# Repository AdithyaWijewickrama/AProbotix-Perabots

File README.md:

# AProbotix-Perabots

This repo holds team AProbotix's work for the PeraBots 2026 competition
(University category), Faculty of Engineering, University of Ruhuna.

| Folder | Round | What it is |
|---|---|---|
| [`Phase 01 - Online Round/`](Phase%2001%20-%20Online%20Round/) | Online (simulation) round | Webots solution submitted for round 1. Includes the TwoWheelRobot controller, test worlds, the sim lab and the submission zip builder |
| [`Phase 02 - Final Round/`](Phase%2002%20-%20Final%20Round/) | Final (physical) round – "The Nine Seals of Pera" | GuardianBot: Webots simulation of all 3 trials, plus the hardware (PCB, laser-cut acrylic, 3-D prints, parts list and build guide) |

## Phase 01 – Online Round

This is the original first-round project, moved into its own folder unchanged. Paths below
are relative to `Phase 01 - Online Round/`:

- `controllers/`, `protos/`, `worlds/`: working copy with comments. Open `worlds/Arena.wbt` in Webots R2025a.
- `submission/`: clean copy built by `make_submission_zip.py` (do not edit by hand).
- `test/`: test worlds, test report, tools and the sim lab (`test/tools/lab/start_lab.bat`).
- `CONTROLLER_EXPLANATION.md`, `DEVELOPMENT_NOTES.md`: write-ups of the controller.

## Phase 02 – Final Round

Start with [`Phase 02 - Final Round/README.md`](Phase%2002%20-%20Final%20Round/README.md).
Quick links:

- Simulation: open `Phase 02 - Final Round/simulation/worlds/perabots_arena.wbt` in Webots R2025a.
- Build guide and parts list: `Phase 02 - Final Round/docs/GuardianBot_build_guide_and_BOM.md`.
- PCB to order: `Phase 02 - Final Round/hardware/pcb/guardianbot_main_gerbers_JLCPCB.zip`.
- Laser cutting: `Phase 02 - Final Round/hardware/acrylic/`. 3-D printing: `Phase 02 - Final Round/hardware/3d_prints/`.

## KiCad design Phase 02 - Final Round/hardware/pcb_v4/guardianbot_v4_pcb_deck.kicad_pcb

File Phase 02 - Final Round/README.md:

# Phase 02 – Final Round: "The Nine Seals of Pera"

PeraBots 2026, University category, final round (physical robot) – team AProbotix.

Our robot is **GuardianBot v4.2**: a 150 mm round robot built from the parts the team really owns. v4.2 is v4.1 with the camera on an SG90 tilt servo, so one look reads the whole Section 3 board (`test/FIXES.md`, Fix 4); the tilting camera mast is in `hardware/3d_prints` (camera_mast + camera_tilt_bracket).

- **Controllers:**
  - Arduino Mega 2560: real-time body, mounted upside-down on the PCB deck.
  - ESP32-S3 N16R8 with an OV7670 camera: brain on core 1, camera on core 0. It sees maze tiles 1–2 cells ahead.
- **Drive:** DRV8833 with two 6 V 300 rpm N20 encoder motors, on a 2S LiPo.
- **Sensors:**
  - 8 × VL53L0X time-of-flight: front, ±45°, two per side for wall alignment, back
  - 2 × HC-SR04
  - 2 × TCS3200 colour: floor tiles and piece colour
  - Pololu QTR-8RC line array
  - L3G4200D gyro
- **User interface:** 1 × 4 keypad and a 128 × 32 OLED.
- **Gripper:** a rear capture pocket with two Kpower M0170 servo arms.
- **Middle floor:** a PCB that carries all the wiring, with keyed JST-XH sockets. A vero board can replace it.

Everything physical is generated from one file of dimensions, `hardware/cad/guardianbot_geometry.py`: the Webots model, the laser-cut decks and the 3-D prints.

**Start here: [`docs/GuardianBot_v4.2_build_guide.md`](docs/GuardianBot_v4.2_build_guide.md).** It covers:

- what changed from v3, and why
- the parts
- the Sri Lankan shopping list (about Rs 15,900; about Rs 11,400 with a vero board)
- the PCB deck and power wiring
- the pin map
- the build order, calibration and the competition procedure

| What | Where |
|---|---|
| Arduino Mega firmware (body: encoders, wheel PID, gyro, 8 ToF, line, sonar, colour, servos, keypad, OLED, link) | `firmware/mega_body/` |
| ESP32-S3 firmware (brain: Sections 1–3, the same strategy as the simulation, plus the OV7670 camera task; no Wi-Fi) | `firmware/esp32s3_brain/` |
| **Test-bench firmware**: Wi-Fi web page for sensors, manual drive, camera, calibration and CSV logs (bench only) | `firmware/esp32s3_testbench/` |
| The same test page for the **simulated** robot (open `testbench.wbt`, then http://localhost:8080) | `simulation/controllers/testbench_sim/` |
| Software-in-the-loop: the real ESP32 C++ drives the Webots robot | `firmware/sil/` + `simulation/controllers/mega_sil/` |
| Host compile check of all three sketches | `firmware/hostcheck/check.sh` |
| **Circuit simulation (like Tinkercad)**: the real Mega firmware on a virtual Mega in Wokwi, every sensor as a custom chip with sliders; checked by unit tests and a simavr co-simulation | `simulation/wokwi/` |
| **SPICE checks** of the PCB deck: link levels and timing at 250 kbaud, battery divider, buzzer driver, power-rail dips | `hardware/spice/` |
| **PCB mid deck** (144 mm round, through-hole, for a local PCB shop) | `hardware/pcb_v4/`, made by `hardware/cad/deck_v4/` |
| **Every earlier version + comparison website** (bodies, PCBs, budget, speed, weight, parts) | `versions/` (website on GitHub Pages, with a 3-D viewer for the PCBs, printed parts and decks) |

Latest Webots results, 0 collisions in every run:

| Run | Section 1 | Maze done | END reached |
|---|---|---|---|
| Python controller, full mission, timed by the neutral judge | 24.1 s | 61.6 s | **153.6 s** |
| ESP32-S3 brain firmware + emulated Mega and camera (software-in-the-loop), full mission | 33.2 s | 77.3 s | **175.6 s** |
| ESP32-S3 brain firmware, Section 3 restart with the saved clues | | | **131.5 s** |

## Folder map

| Folder | What is inside |
|---|---|
| `docs/` | Final-round rulebook (PDF and extracted text), **`GuardianBot_v4.2_build_guide.md`**, `TEST_PLAN.md`, robot renders, rulebook figures, sample run log |
| `simulation/` | Webots R2025a project: arena, robot, controllers |
| `simulation/worlds/` | `perabots_arena.wbt` (full mission), `section3_start.wbt` (restart at Section 3), `guardian_hw_test.wbt` (gripper/sensor self-test), `testbench.wbt` (test web page on the simulated robot), `Arena.wbt` (same as perabots_arena) |
| `simulation/protos/` | `Arena.proto` (Section 3 rebuilt from rulebook Figure 1), `Obstacles.proto`, `GuardianBot.proto` (generated) |
| `simulation/controllers/` | `main_controller` (Sections 1, 2, 3; writes `run_log.txt` and `clues.json`), `mega_sil` (runs the ESP32 firmware in the loop) and `guardian_hw_test` |
| `simulation/make_guardianbot.py`, `make_world.py` | Regenerate the robot PROTO / the worlds |
| `simulation/tools/` | `rebuild_section3.py`: rewrites the Section 3 part of `Arena.proto` |
| `firmware/` | Robot firmware (see above) |
| `hardware/cad/` | Generator scripts: `guardianbot_geometry.py` (all dimensions), `make_acrylic_dxf.py`, `make_printed_parts.py`, `autoroute.py` (PCB router), `deck_v4/` (PCB deck: parts + nets, placement, routing, Gerbers, schematic, render) |
| `hardware/acrylic/` | Laser-cut DXF + STL: base and top decks (3 mm), the vero-fallback mid deck, and all three on one sheet |
| `hardware/3d_prints/` | STL and STEP for the 15 printed part types (ToF posts, camera mast, gripper, pocket, ...) |
| `hardware/pcb_v4/` | PCB mid deck: KiCad project, schematic PDF, Gerbers zip, toner-transfer PDFs, BOM, positions, DRC report, render |
| `analysis/` | Early investigation scripts (maze/obstacle extraction from the rulebook and the Phase 01 arena, frame checks) and the images extracted from the rulebook |
| `versions/` | Every earlier version with a `spec.yaml` (v1.0 … v4.0) and its files: e.g. v2.0 with its PCB, v3.3 with the ESP32-S3 firmware, the Mega shield PCB and the v3 guide. Also the neutral judge used to time them, and the comparison website |

## Run the simulation

1. Open `simulation/worlds/perabots_arena.wbt` in Webots R2025a.
2. Press run (fast mode recommended). The controller prints its progress and also writes
   `simulation/controllers/main_controller/run_log.txt`.

Last full run (v4): Section 1 at 24 s, maze done at 62 s (3 blue + 2 green tiles),
piece placed in position 7, END reached at 153.6 s, 0 collisions.

**Run the real firmware in Webots (software-in-the-loop).**

1. Build the brain with `firmware/sil/build_sil.sh` (Linux, WSL or MinGW g++).
2. Set the robot's `controller` to `mega_sil`.
3. Run as usual. The brain's log goes to `simulation/controllers/mega_sil/sil_log.txt`.

`section3_start.wbt` starts the robot in the maze exit cell. It uses the clues saved in
`clues.json`, as the real robot would after a judge-ordered restart.

## Regenerate files

```
cd simulation
python make_guardianbot.py      # protos/GuardianBot.proto
python make_world.py            # worlds/*.wbt

cd ../hardware/cad
python deck_v4/make_deck.py route                     # PCB mid deck: place + autoroute (KiCad 7 python, shapely)
python deck_v4/fix_unrouted.py --rip-gnd --clr 0.2    # finish the last connections, re-route GND, DRC
python deck_v4/make_deck.py fab                       # Gerbers, drill, toner PDFs, BOM
python deck_v4/make_deck_schematic.py                                 # its schematic
python make_acrylic_dxf.py      # ../acrylic/*.dxf + .stl     (needs: pip install cadquery ezdxf shapely)
python make_printed_parts.py    # ../3d_prints/*.stl/.step    (needs: pip install cadquery)
```

Change a dimension in `hardware/cad/guardianbot_geometry.py`, then rerun the generators.
The robot model, acrylic and prints stay consistent with each other.

## Key facts from the rulebook

- Arena 2.44 × 3.66 m in 3 sections. Section 3 has a 3 × 3 board (122 × 92 cm, 2 cm lines),
  with green/blue collection pads and END at the far side.
- Clues: blue tiles → Cylinder 1, green tiles → Cube 1, right turns → Cylinder 2, left turns → Cube 2.
  Positions follow the Lo Shu magic square: 1 is the middle of the entrance row, 6 is on the robot's left.
- Robot must fit 20 × 20 × 20 cm. A 2-minute calibration with a CAL button is allowed (keypad K4).
  You get 3 attempts in 15 minutes.

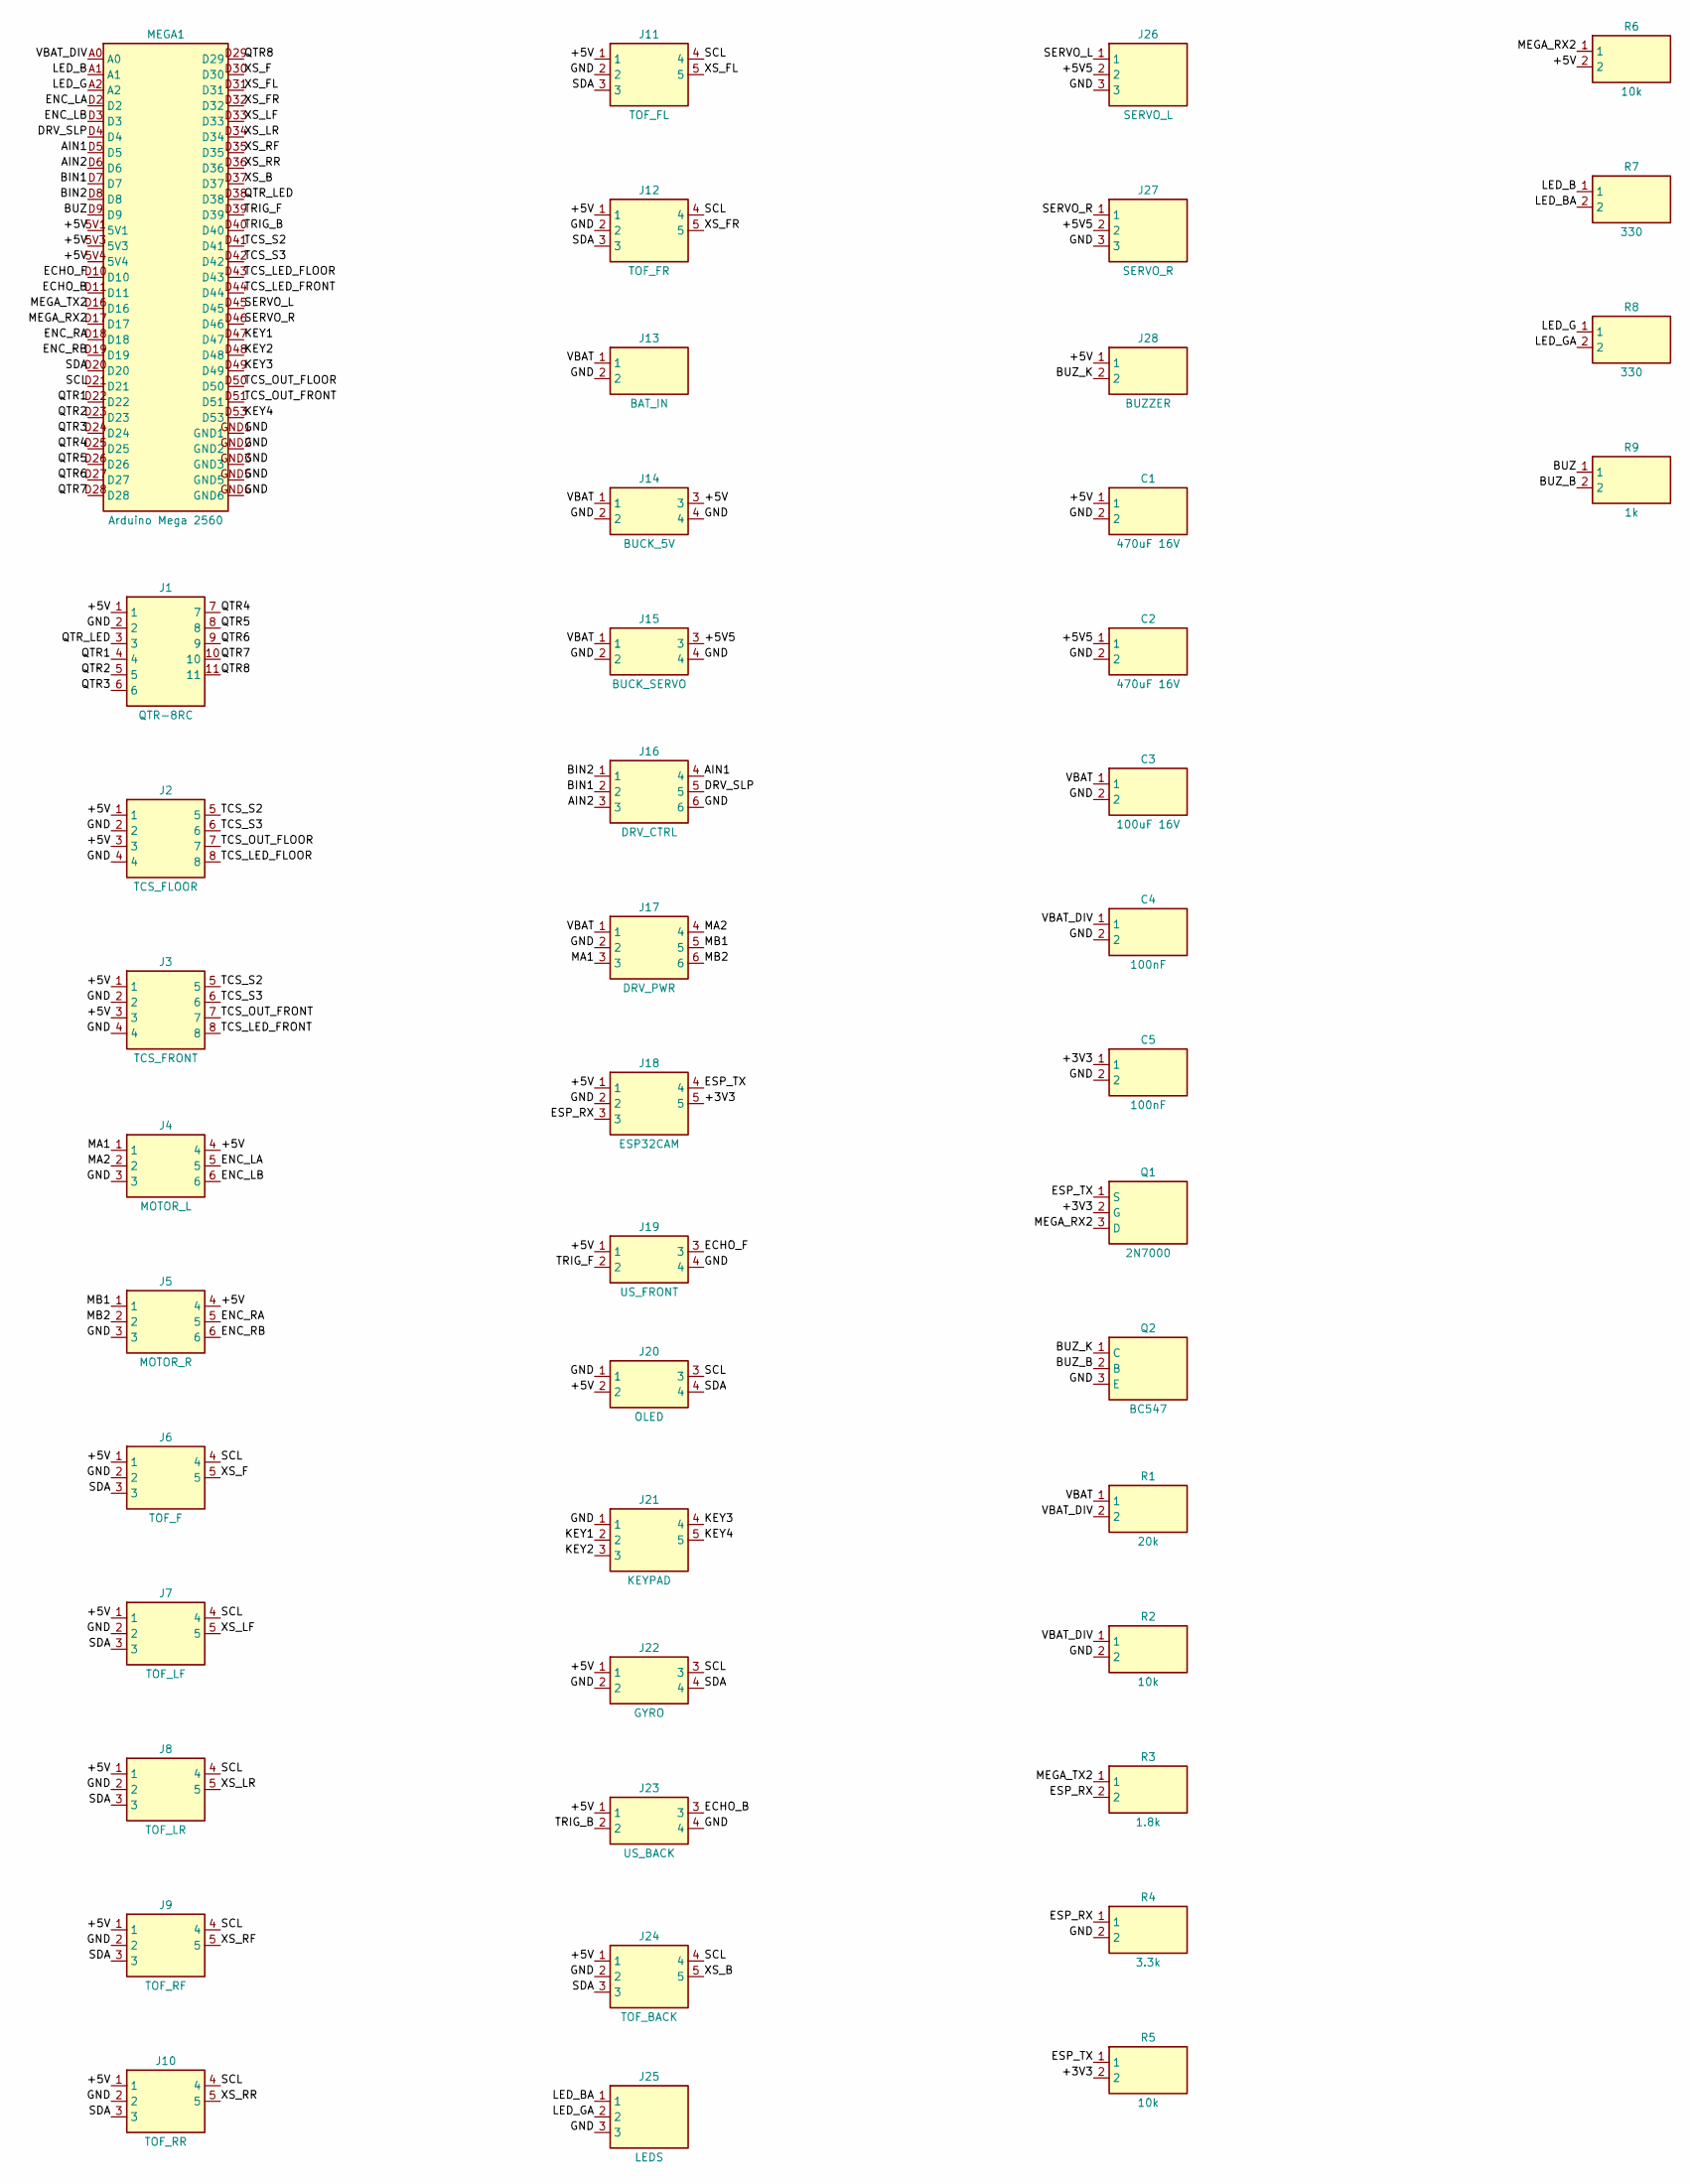
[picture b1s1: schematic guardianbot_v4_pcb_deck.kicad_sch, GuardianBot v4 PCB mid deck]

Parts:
C1, C2: 470uF 16V; CP_Radial_D10.0mm_P5.00mm
C3: 100uF 16V; CP_Radial_D6.3mm_P2.50mm
C4, C5: 100nF; C_Disc_D3.0mm_W1.6mm_P2.50mm
J1: QTR-8RC; JST_XH_B11B-XH-A_1x11_P2.50mm_Vertical
J2: TCS_FLOOR; JST_XH_B8B-XH-A_1x08_P2.50mm_Vertical
J3: TCS_FRONT; JST_XH_B8B-XH-A_1x08_P2.50mm_Vertical
J4: MOTOR_L; JST_XH_B6B-XH-A_1x06_P2.50mm_Vertical
J5: MOTOR_R; JST_XH_B6B-XH-A_1x06_P2.50mm_Vertical
J6: TOF_F; JST_XH_B5B-XH-A_1x05_P2.50mm_Vertical
J7: TOF_LF; JST_XH_B5B-XH-A_1x05_P2.50mm_Vertical
J8: TOF_LR; JST_XH_B5B-XH-A_1x05_P2.50mm_Vertical
J9: TOF_RF; JST_XH_B5B-XH-A_1x05_P2.50mm_Vertical
J10: TOF_RR; JST_XH_B5B-XH-A_1x05_P2.50mm_Vertical
J11: TOF_FL; JST_XH_B5B-XH-A_1x05_P2.50mm_Vertical
J12: TOF_FR; JST_XH_B5B-XH-A_1x05_P2.50mm_Vertical
J13: BAT_IN; JST_XH_B2B-XH-A_1x02_P2.50mm_Vertical
J14: BUCK_5V; JST_XH_B4B-XH-A_1x04_P2.50mm_Vertical
J15: BUCK_SERVO; JST_XH_B4B-XH-A_1x04_P2.50mm_Vertical
J16: DRV_CTRL; PinHeader_1x06_P2.54mm_Vertical
J17: DRV_PWR; PinHeader_1x06_P2.54mm_Vertical
J18: ESP32CAM; JST_XH_B5B-XH-A_1x05_P2.50mm_Vertical
J19: US_FRONT; JST_XH_B4B-XH-A_1x04_P2.50mm_Vertical
J20: OLED; JST_XH_B4B-XH-A_1x04_P2.50mm_Vertical
J21: KEYPAD; JST_XH_B5B-XH-A_1x05_P2.50mm_Vertical
J22: GYRO; JST_XH_B4B-XH-A_1x04_P2.50mm_Vertical
J23: US_BACK; JST_XH_B4B-XH-A_1x04_P2.50mm_Vertical
J24: TOF_BACK; JST_XH_B5B-XH-A_1x05_P2.50mm_Vertical
J25: LEDS; JST_XH_B3B-XH-A_1x03_P2.50mm_Vertical
J26: SERVO_L; PinHeader_1x03_P2.54mm_Vertical
J27: SERVO_R; PinHeader_1x03_P2.54mm_Vertical
J28: BUZZER; JST_XH_B2B-XH-A_1x02_P2.50mm_Vertical
MEGA1: Arduino Mega 2560
Q1: 2N7000; TO-92_Inline_Wide
Q2: BC547; TO-92_Inline_Wide
R1: 20k; R_Axial_DIN0207_L6.3mm_D2.5mm_P7.62mm_Horizontal
R2, R5, R6: 10k; R_Axial_DIN0207_L6.3mm_D2.5mm_P7.62mm_Horizontal
R3: 1.8k; R_Axial_DIN0207_L6.3mm_D2.5mm_P7.62mm_Horizontal
R4: 3.3k; R_Axial_DIN0207_L6.3mm_D2.5mm_P7.62mm_Horizontal
R7, R8: 330; R_Axial_DIN0207_L6.3mm_D2.5mm_P7.62mm_Horizontal
R9: 1k; R_Axial_DIN0207_L6.3mm_D2.5mm_P7.62mm_Horizontal

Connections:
+3V3: C5.1, J18.5, Q1.2 (G), R5.2
+5V: C1.1, J1.1, J2.1, J2.3, J3.1, J3.3, J4.4, J5.4, J6.1, J7.1, J8.1, J9.1, J10.1, J11.1, J12.1, J14.3, J18.1, J19.1, J20.2, J22.1, J23.1, J24.1, J28.1, MEGA1.5V1, MEGA1.5V3, MEGA1.5V4, R6.2
+5V5: C2.1, J15.3, J26.2, J27.2
AIN1: J16.4, MEGA1.D5
AIN2: J16.3, MEGA1.D6
BIN1: J16.2, MEGA1.D7
BIN2: J16.1, MEGA1.D8
BUZ: MEGA1.D9, R9.1
BUZ_B: Q2.2 (B), R9.2
BUZ_K: J28.2, Q2.1 (C)
DRV_SLP: J16.5, MEGA1.D4
ECHO_B: J23.3, MEGA1.D11
ECHO_F: J19.3, MEGA1.D10
ENC_LA: J4.5, MEGA1.D2
ENC_LB: J4.6, MEGA1.D3
ENC_RA: J5.5, MEGA1.D18
ENC_RB: J5.6, MEGA1.D19
ESP_RX: J18.3, R3.2, R4.1
ESP_TX: J18.4, Q1.1 (S), R5.1
GND: C1.2, C2.2, C3.2, C4.2, C5.2, J1.2, J2.2, J2.4, J3.2, J3.4, J4.3, J5.3, J6.2, J7.2, J8.2, J9.2, J10.2, J11.2, J12.2, J13.2, J14.2, J14.4, J15.2, J15.4, J16.6, J17.2, J18.2, J19.4, J20.1, J21.1, J22.2, J23.4, J24.2, J25.3, J26.3, J27.3, MEGA1.GND1, MEGA1.GND2, MEGA1.GND3, MEGA1.GND5, MEGA1.GND6, Q2.3 (E), R2.2, R4.2
KEY1: J21.2, MEGA1.D47
KEY2: J21.3, MEGA1.D48
KEY3: J21.4, MEGA1.D49
KEY4: J21.5, MEGA1.D53
LED_B: MEGA1.A1, R7.1
LED_BA: J25.1, R7.2
LED_G: MEGA1.A2, R8.1
LED_GA: J25.2, R8.2
MA1: J4.1, J17.3
MA2: J4.2, J17.4
MB1: J5.1, J17.5
MB2: J5.2, J17.6
MEGA_RX2: MEGA1.D17, Q1.3 (D), R6.1
MEGA_TX2: MEGA1.D16, R3.1
QTR1: J1.4, MEGA1.D22
QTR2: J1.5, MEGA1.D23
QTR3: J1.6, MEGA1.D24
QTR4: J1.7, MEGA1.D25
QTR5: J1.8, MEGA1.D26
QTR6: J1.9, MEGA1.D27
QTR7: J1.10, MEGA1.D28
QTR8: J1.11, MEGA1.D29
QTR_LED: J1.3, MEGA1.D38
SCL: J6.4, J7.4, J8.4, J9.4, J10.4, J11.4, J12.4, J20.3, J22.3, J24.4, MEGA1.D21
SDA: J6.3, J7.3, J8.3, J9.3, J10.3, J11.3, J12.3, J20.4, J22.4, J24.3, MEGA1.D20
SERVO_L: J26.1, MEGA1.D45
SERVO_R: J27.1, MEGA1.D46
TCS_LED_FLOOR: J2.8, MEGA1.D43
TCS_LED_FRONT: J3.8, MEGA1.D44
TCS_OUT_FLOOR: J2.7, MEGA1.D50
TCS_OUT_FRONT: J3.7, MEGA1.D51
TCS_S2: J2.5, J3.5, MEGA1.D41
TCS_S3: J2.6, J3.6, MEGA1.D42
TRIG_B: J23.2, MEGA1.D40
TRIG_F: J19.2, MEGA1.D39
VBAT: C3.1, J13.1, J14.1, J15.1, J17.1, R1.1
VBAT_DIV: C4.1, MEGA1.A0, R1.2, R2.1
XS_B: J24.5, MEGA1.D37
XS_F: J6.5, MEGA1.D30
XS_FL: J11.5, MEGA1.D31
XS_FR: J12.5, MEGA1.D32
XS_LF: J7.5, MEGA1.D33
XS_LR: J8.5, MEGA1.D34
XS_RF: J9.5, MEGA1.D35
XS_RR: J10.5, MEGA1.D36

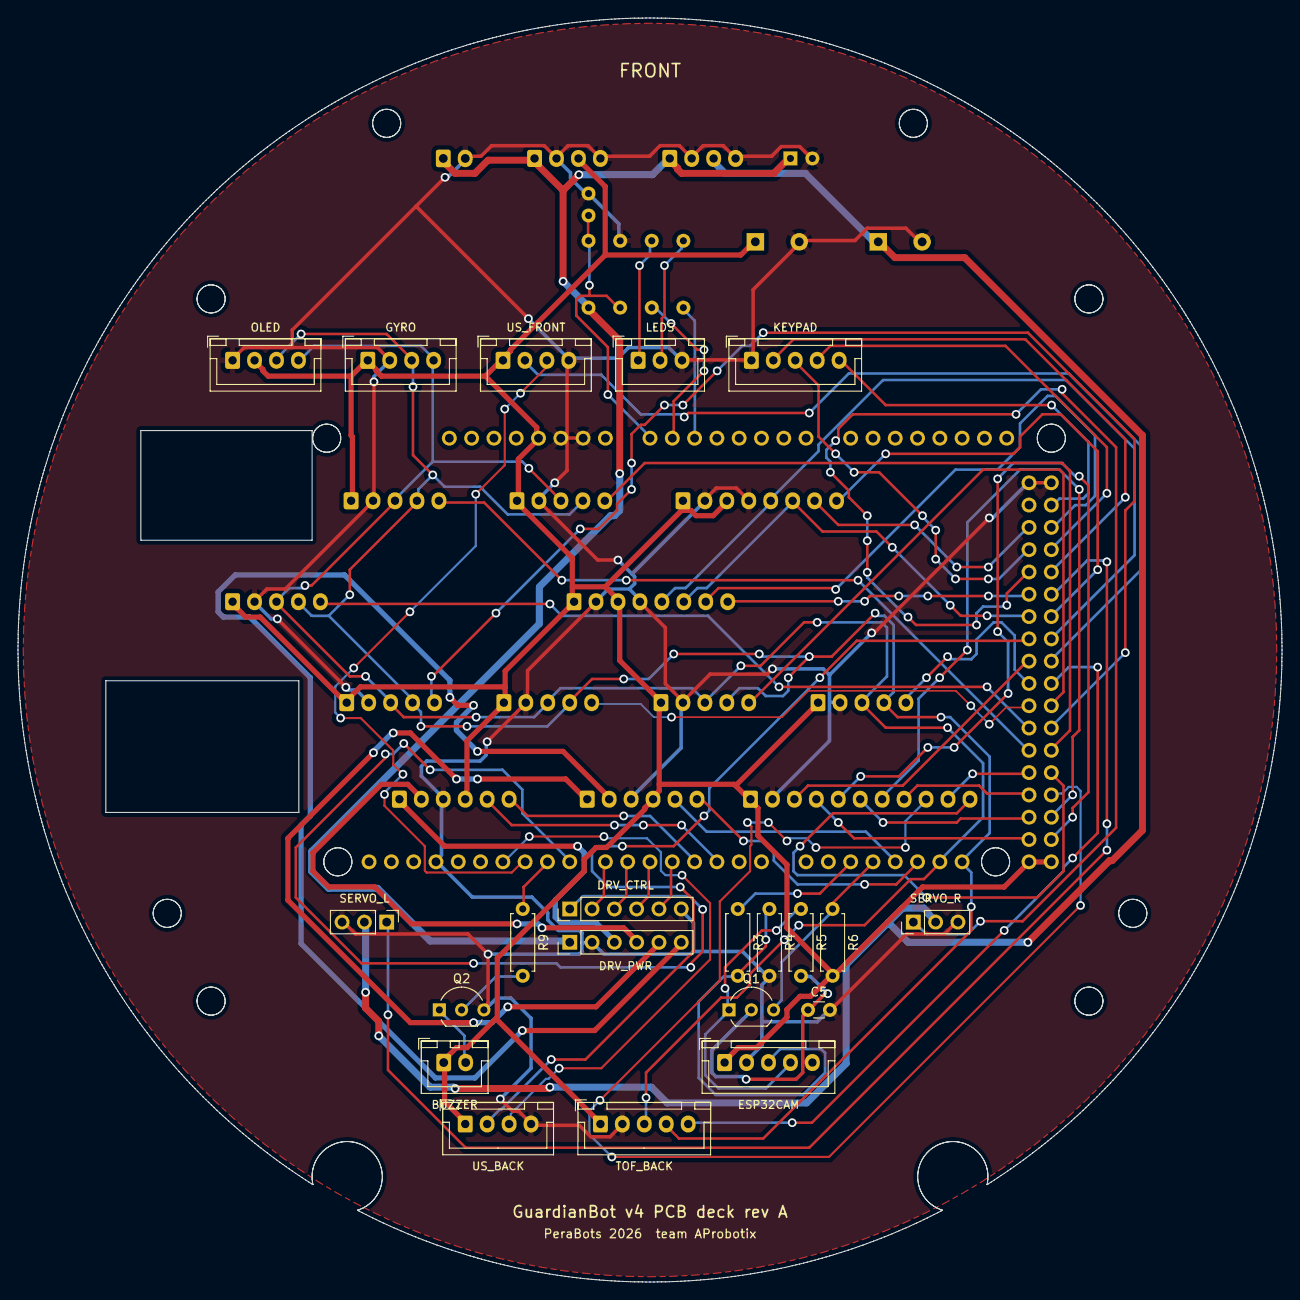
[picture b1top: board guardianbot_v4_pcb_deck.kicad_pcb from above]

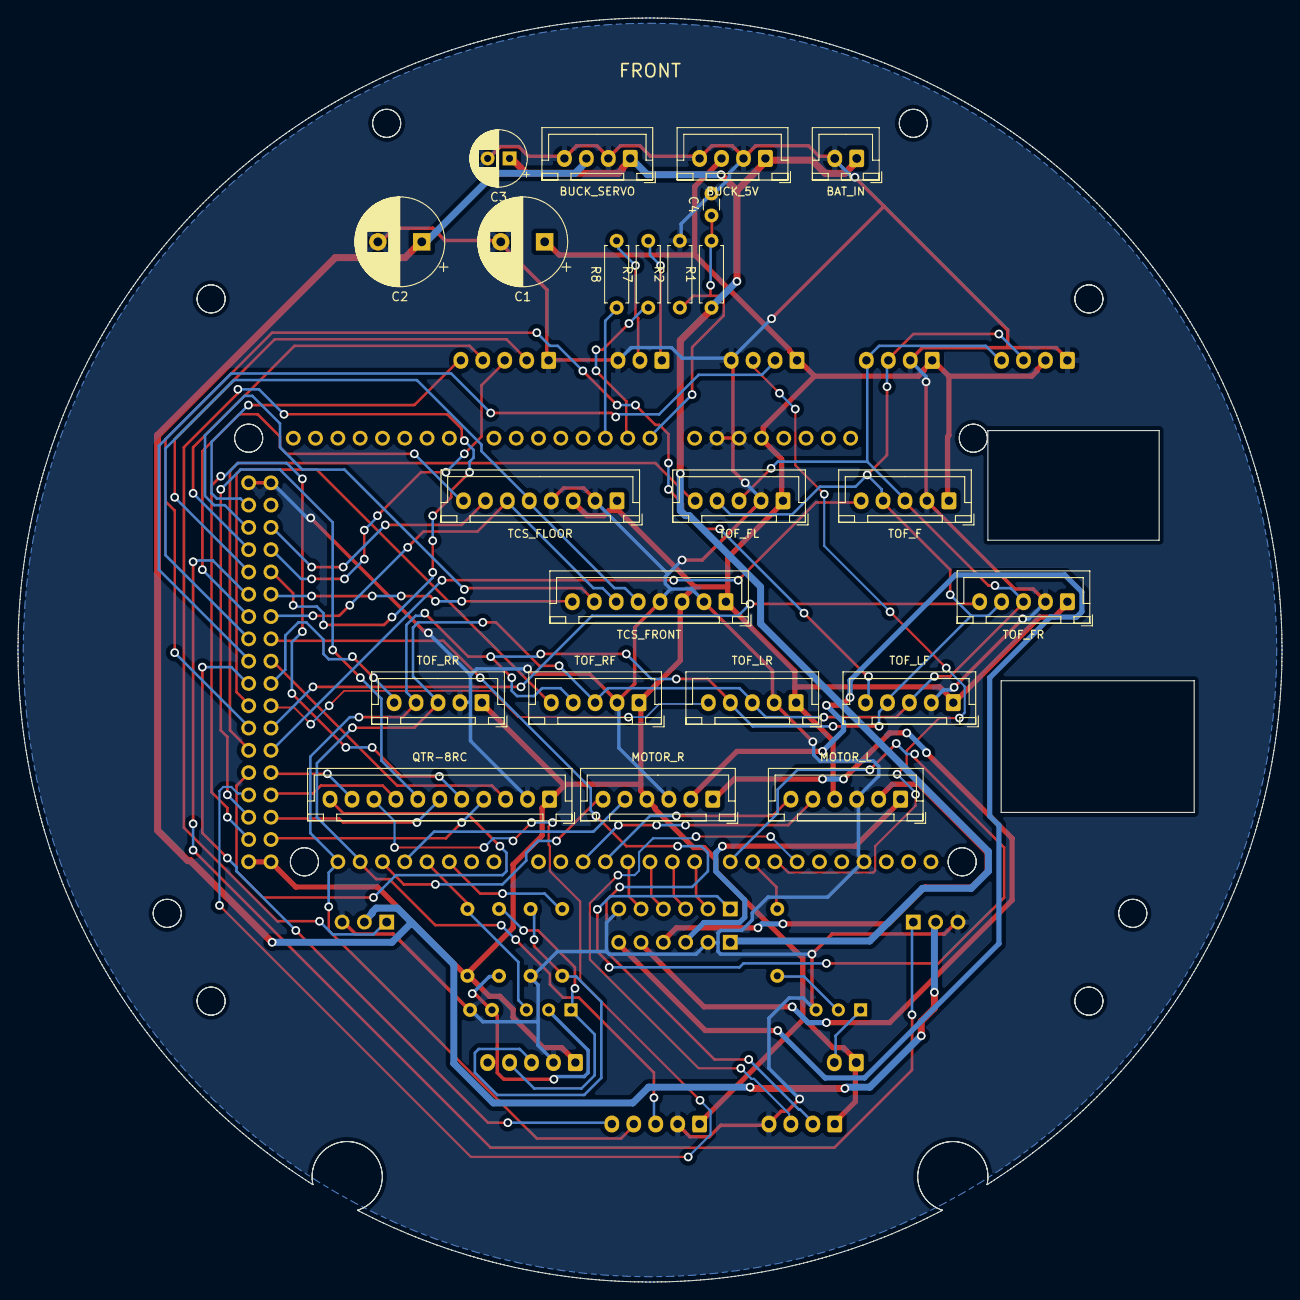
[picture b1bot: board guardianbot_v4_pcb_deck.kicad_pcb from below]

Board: 2 copper layers, 144.0 x 144.0 mm, 45 parts (23 on the bottom side), 65 nets.

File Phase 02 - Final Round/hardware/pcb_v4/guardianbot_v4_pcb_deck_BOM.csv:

Qty,Value,Footprint,References,Note
1,"long male headers (pin 20 mm+): 8,8,8,8,10,8,8 pin + 2x18",-,MEGA1,"solder in the deck, the Mega plugs on upside-down 11 mm above (4x M3 x 11 mm spacers)"
2,470uF 16V,CP_Radial_D10.0mm_P5.00mm,C1 C2,5 V bulk
1,100uF 16V,CP_Radial_D6.3mm_P2.50mm,C3,battery
2,100nF,C_Disc_D3.0mm_W1.6mm_P2.50mm,C4 C5,ADC filter
1,QTR-8RC,JST_XH_B11B-XH-A_1x11_P2.50mm_Vertical,J1,VCC GND LEDON 1..8 (sensor 1 = right-most)
1,TOF_RR,JST_XH_B5B-XH-A_1x05_P2.50mm_Vertical,J10,VL53L0X: VIN GND SDA SCL XSHUT
1,TOF_FL,JST_XH_B5B-XH-A_1x05_P2.50mm_Vertical,J11,VL53L0X: VIN GND SDA SCL XSHUT
1,TOF_FR,JST_XH_B5B-XH-A_1x05_P2.50mm_Vertical,J12,VL53L0X: VIN GND SDA SCL XSHUT
1,BAT_IN,JST_XH_B2B-XH-A_1x02_P2.50mm_Vertical,J13,from the power switch (2S LiPo 7.4 V)
1,BUCK_5V,JST_XH_B4B-XH-A_1x04_P2.50mm_Vertical,J14,LM2596 set to 5.0 V: IN+ IN- OUT+ OUT-
1,BUCK_SERVO,JST_XH_B4B-XH-A_1x04_P2.50mm_Vertical,J15,HW-319 set to 5.5 V: IN+ IN- OUT+ OUT-
1,DRV_CTRL,PinHeader_1x06_P2.54mm_Vertical,J16,wire to the DRV8833 carrier: BIN2 BIN1 AIN2 AIN1 SLP GND
1,DRV_PWR,PinHeader_1x06_P2.54mm_Vertical,J17,wire to the DRV8833 carrier: VIN GND AOUT1 AOUT2 BOUT1 BOUT2
1,ESP32CAM,JST_XH_B5B-XH-A_1x05_P2.50mm_Vertical,J18,to the ESP32-CAM on the mast: 5V GND U0R(GPIO15 RX) GPIO14(TX) 3V3 (3.3 V comes from the CAM board)
1,US_FRONT,JST_XH_B4B-XH-A_1x04_P2.50mm_Vertical,J19,HC-SR04: VCC TRIG ECHO GND
1,TCS_FLOOR,JST_XH_B8B-XH-A_1x08_P2.50mm_Vertical,J2,TCS3200: VCC GND S0 S1 S2 S3 OUT LED
1,OLED,JST_XH_B4B-XH-A_1x04_P2.50mm_Vertical,J20,SSD1306 128x32: GND VCC SCL SDA
1,KEYPAD,JST_XH_B5B-XH-A_1x05_P2.50mm_Vertical,J21,1x4 membrane keypad: COM K1 K2 K3 K4
1,GYRO,JST_XH_B4B-XH-A_1x04_P2.50mm_Vertical,J22,GY-50 L3G4200D: VCC GND SCL SDA
1,US_BACK,JST_XH_B4B-XH-A_1x04_P2.50mm_Vertical,J23,HC-SR04: VCC TRIG ECHO GND
1,TOF_BACK,JST_XH_B5B-XH-A_1x05_P2.50mm_Vertical,J24,VL53L0X: VIN GND SDA SCL XSHUT
1,LEDS,JST_XH_B3B-XH-A_1x03_P2.50mm_Vertical,J25,"blue LED +, green LED +, common GND"
1,SERVO_L,PinHeader_1x03_P2.54mm_Vertical,J26,M0170 servo: S + -
1,SERVO_R,PinHeader_1x03_P2.54mm_Vertical,J27,M0170 servo: S + -
1,BUZZER,JST_XH_B2B-XH-A_1x02_P2.50mm_Vertical,J28,5 V active buzzer: + -
1,TCS_FRONT,JST_XH_B8B-XH-A_1x08_P2.50mm_Vertical,J3,TCS3200: VCC GND S0 S1 S2 S3 OUT LED
1,MOTOR_L,JST_XH_B6B-XH-A_1x06_P2.50mm_Vertical,J4,N20 encoder motor: M1 M2 GND VCC A B
1,MOTOR_R,JST_XH_B6B-XH-A_1x06_P2.50mm_Vertical,J5,N20 encoder motor: M1 M2 GND VCC A B
1,TOF_F,JST_XH_B5B-XH-A_1x05_P2.50mm_Vertical,J6,VL53L0X: VIN GND SDA SCL XSHUT
1,TOF_LF,JST_XH_B5B-XH-A_1x05_P2.50mm_Vertical,J7,VL53L0X: VIN GND SDA SCL XSHUT
1,TOF_LR,JST_XH_B5B-XH-A_1x05_P2.50mm_Vertical,J8,VL53L0X: VIN GND SDA SCL XSHUT
1,TOF_RF,JST_XH_B5B-XH-A_1x05_P2.50mm_Vertical,J9,VL53L0X: VIN GND SDA SCL XSHUT
1,2N7000,TO-92_Inline_Wide,Q1,level shifter ESP TX -> Mega RX2 (S G D)
1,BC547,TO-92_Inline_Wide,Q2,buzzer driver (C B E)
1,20k,R_Axial_DIN0207_L6.3mm_D2.5mm_P7.62mm_Horizontal,R1,battery divider top
3,10k,R_Axial_DIN0207_L6.3mm_D2.5mm_P7.62mm_Horizontal,R2 R5 R6,battery divider bottom (A0 = VBAT / 3)
1,1.8k,R_Axial_DIN0207_L6.3mm_D2.5mm_P7.62mm_Horizontal,R3,Mega TX2 -> ESP RX divider top
1,3.3k,R_Axial_DIN0207_L6.3mm_D2.5mm_P7.62mm_Horizontal,R4,divider bottom: 5 V -> 3.2 V
2,330,R_Axial_DIN0207_L6.3mm_D2.5mm_P7.62mm_Horizontal,R7 R8,blue LED
1,1k,R_Axial_DIN0207_L6.3mm_D2.5mm_P7.62mm_Horizontal,R9,buzzer transistor base

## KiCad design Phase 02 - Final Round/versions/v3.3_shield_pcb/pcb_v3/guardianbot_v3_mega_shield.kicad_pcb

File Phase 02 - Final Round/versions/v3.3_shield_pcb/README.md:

# GuardianBot v3.3 files (Mega + ESP32-S3 + ESP32-CAM, Mega shield PCB)

These are the v3.3 files that v4.0 replaced. They are kept here for reference and comparison.
The complete v3.3 tree, which runs as it was, is git tag `v3.3-pcb`. Its numbers are in `spec.yaml` in this folder.

| Folder / file | What it was |
|---|---|
| `firmware/esp32s3_brain/` | ESP32-S3 brain firmware (v3.3 version; v4.0 used `versions/v4.0_esp32cam_pcbdeck/firmware/esp32cam_brain/`, v4.1 uses the top-level `firmware/esp32s3_brain/`) |
| `firmware/esp32cam_vision/` | ESP32-CAM camera-only firmware (v4.0: the camera task in `esp32cam_brain`; v4.1: `firmware/esp32s3_brain/cam_ov7670.h`) |
| `cad/shield_v3/` | Mega shield PCB generator (paths assume its old place in `hardware/cad/`) |
| `pcb_v3/` | Mega shield KiCad project, Gerbers, toner PDFs, BOM, DRC |
| `GuardianBot_v3_build_guide.md` | v3 build guide and Rs 15,000 shopping list |
| `acrylic/`, `3d_prints/` | acrylic mid deck, Sharp IR mounts, 32 mm deck spacers |

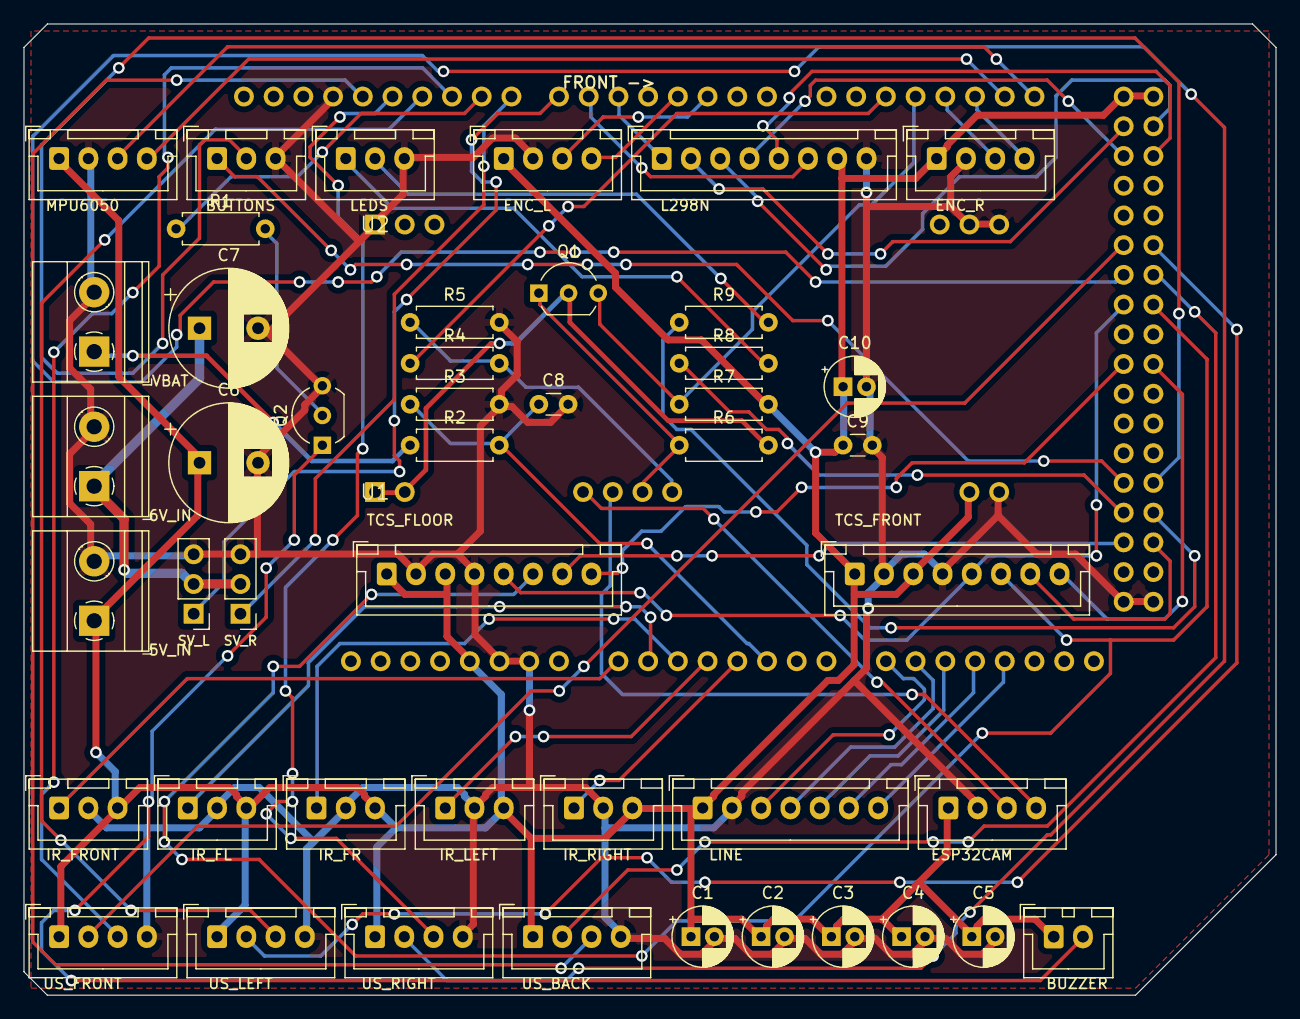
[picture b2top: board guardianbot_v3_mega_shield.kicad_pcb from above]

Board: 2 copper layers, 107.0 x 83.0 mm, 49 parts (0 on the bottom side), 59 nets.

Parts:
C1, C2, C3, C4, C5: 10uF; CP_Radial_D5.0mm_P2.00mm
C6, C7: 470uF 16V; CP_Radial_D10.0mm_P5.00mm
C8, C9: 100nF; C_Disc_D3.0mm_W1.6mm_P2.50mm
C10: 100uF 10V; CP_Radial_D5.0mm_P2.00mm
J1: US_FRONT; JST_XH_B4B-XH-A_1x04_P2.50mm_Vertical
J2: US_LEFT; JST_XH_B4B-XH-A_1x04_P2.50mm_Vertical
J3: US_RIGHT; JST_XH_B4B-XH-A_1x04_P2.50mm_Vertical
J4: US_BACK; JST_XH_B4B-XH-A_1x04_P2.50mm_Vertical
J5: IR_FRONT; JST_XH_B3B-XH-A_1x03_P2.50mm_Vertical
J6: IR_FL; JST_XH_B3B-XH-A_1x03_P2.50mm_Vertical
J7: IR_FR; JST_XH_B3B-XH-A_1x03_P2.50mm_Vertical
J8: IR_LEFT; JST_XH_B3B-XH-A_1x03_P2.50mm_Vertical
J9: IR_RIGHT; JST_XH_B3B-XH-A_1x03_P2.50mm_Vertical
J10: TCS_FLOOR; JST_XH_B8B-XH-A_1x08_P2.50mm_Vertical
J11: TCS_FRONT; JST_XH_B8B-XH-A_1x08_P2.50mm_Vertical
J12: LINE; JST_XH_B7B-XH-A_1x07_P2.50mm_Vertical
J13: L298N; JST_XH_B8B-XH-A_1x08_P2.50mm_Vertical
J14: MPU6050; JST_XH_B4B-XH-A_1x04_P2.50mm_Vertical
J15: ENC_L; JST_XH_B4B-XH-A_1x04_P2.50mm_Vertical
J16: ENC_R; JST_XH_B4B-XH-A_1x04_P2.50mm_Vertical
J17: ESP32CAM; JST_XH_B4B-XH-A_1x04_P2.50mm_Vertical
J18: BUTTONS; JST_XH_B3B-XH-A_1x03_P2.50mm_Vertical
J19: LEDS; JST_XH_B3B-XH-A_1x03_P2.50mm_Vertical
J20: 5V_IN; TerminalBlock_Phoenix_MKDS-1,5-2-5.08_1x02_P5.08mm_Horizont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
J21: 6V_IN; TerminalBlock_Phoenix_MKDS-1,5-2-5.08_1x02_P5.08mm_Horizont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
J22: VBAT; TerminalBlock_Phoenix_MKDS-1,5-2-5.08_1x02_P5.08mm_Horizont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
J23: SERVO_L; PinHeader_1x03_P2.54mm_Vertical
J24: SERVO_R; PinHeader_1x03_P2.54mm_Vertical
J25: BUZZER; JST_XH_B2B-XH-A_1x02_P2.50mm_Vertical
MEGA1: Arduino Mega 2560 R3 headers
Q1: 2N7000; TO-92_Inline_Wide
Q2: BC547; TO-92_Inline_Wide
R1: 1k; R_Axial_DIN0207_L6.3mm_D2.5mm_P7.62mm_Horizontal
R2: 20k; R_Axial_DIN0207_L6.3mm_D2.5mm_P7.62mm_Horizontal
R3, R6, R7: 10k; R_Axial_DIN0207_L6.3mm_D2.5mm_P7.62mm_Horizontal
R4: 1.8k; R_Axial_DIN0207_L6.3mm_D2.5mm_P7.62mm_Horizontal
R5: 3.3k; R_Axial_DIN0207_L6.3mm_D2.5mm_P7.62mm_Horizontal
R8, R9: 330; R_Axial_DIN0207_L6.3mm_D2.5mm_P7.62mm_Horizontal
U1: ESP32-S3 DevKitC-1 J1 (1x22 socket)
U2: ESP32-S3 DevKitC-1 J3 (1x22 socket)

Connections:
+3V3: Q1.2, R6.2, U1.1, U1.2
+5V: C1.1, C2.1, C3.1, C4.1, C5.1, C6.1, C9.1, C10.1, J1.1, J2.1, J3.1, J4.1, J5.3, J6.3, J7.3, J8.3, J9.3, J10.1, J10.3, J11.1, J11.3, J12.1, J13.7, J14.1, J15.1, J16.1, J17.1, J20.1, J25.1, MEGA1.5V1, MEGA1.5V3, MEGA1.5V4, R7.2, U1.21
+6V: C7.1, J21.1, J23.2, J24.2
BTN_CAL: J18.2, MEGA1.D47
BTN_START: J18.1, MEGA1.D46
BUZ: MEGA1.D9, R1.1
BUZ_B: Q2.2, R1.2
BUZ_K: J25.2, Q2.1
CAM_RX: J17.4, U1.9
CAM_TX: J17.3, U1.8
ECHO_B: J4.3, MEGA1.D13
ECHO_F: J1.3, MEGA1.D10
ECHO_L: J2.3, MEGA1.D11
ECHO_R: J3.3, MEGA1.D12
ENA: J13.1, MEGA1.D5
ENB: J13.6, MEGA1.D6
ENC_LA: J15.3, MEGA1.D2
ENC_LB: J15.4, MEGA1.D3
ENC_RA: J16.3, MEGA1.D18
ENC_RB: J16.4, MEGA1.D19
ESP_RX: R4.2, R5.1, U1.11
ESP_TX: Q1.1, R6.1, U1.10
GND: C1.2, C2.2, C3.2, C4.2, C5.2, C6.2, C7.2, C8.2, C9.2, C10.2, J1.4, J2.4, J3.4, J4.4, J5.2, J6.2, J7.2, J8.2, J9.2, J10.2, J10.4, J11.2, J11.4, J12.2, J13.8, J14.2, J15.2, J16.2, J17.2, J18.3, J19.3, J20.2, J21.2, J22.2, J23.3, J24.3, MEGA1.GND1, MEGA1.GND2, MEGA1.GND3, MEGA1.GND5, MEGA1.GND6, Q2.3, R3.2, R5.2, U1.22, U2.1, U2.21, U2.22
GS0: J12.3, MEGA1.A8
GS1: J12.4, MEGA1.A9
GS2: J12.5, MEGA1.A10
GS3: J12.6, MEGA1.A11
GS4: J12.7, MEGA1.A12
IN1: J13.2, MEGA1.D22
IN2: J13.3, MEGA1.D23
IN3: J13.4, MEGA1.D24
IN4: J13.5, MEGA1.D25
IR_F: J5.1, MEGA1.A0
IR_FL: J6.1, MEGA1.A1
IR_FR: J7.1, MEGA1.A2
IR_L: J8.1, MEGA1.A3
IR_R: J9.1, MEGA1.A4
LED_B: MEGA1.D48, R8.1
LED_BA: J19.1, R8.2
LED_G: MEGA1.D49, R9.1
LED_GA: J19.2, R9.2
MEGA_RX2: MEGA1.D17, Q1.3, R7.1
MEGA_TX2: MEGA1.D16, R4.1
SCL: J14.3, MEGA1.D21
SDA: J14.4, MEGA1.D20
SERVO_L: J23.1, MEGA1.D7
SERVO_R: J24.1, MEGA1.D8
TCS_LED_FLOOR: J10.8, MEGA1.D38
TCS_LED_FRONT: J11.8, MEGA1.D39
TCS_OUT_FLOOR: J10.7, MEGA1.D50
TCS_OUT_FRONT: J11.7, MEGA1.D51
TCS_S2: J10.5, J11.5, MEGA1.D34
TCS_S3: J10.6, J11.6, MEGA1.D35
TRIG_B: J4.2, MEGA1.D33
TRIG_F: J1.2, MEGA1.D30
TRIG_L: J2.2, MEGA1.D31
TRIG_R: J3.2, MEGA1.D32
VBAT: J22.1, R2.1
VBAT_DIV: C8.1, MEGA1.A5, R2.2, R3.1
